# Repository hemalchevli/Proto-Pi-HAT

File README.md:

Prototying board for the raspberry pi B+. CC-BY-SA-4.0

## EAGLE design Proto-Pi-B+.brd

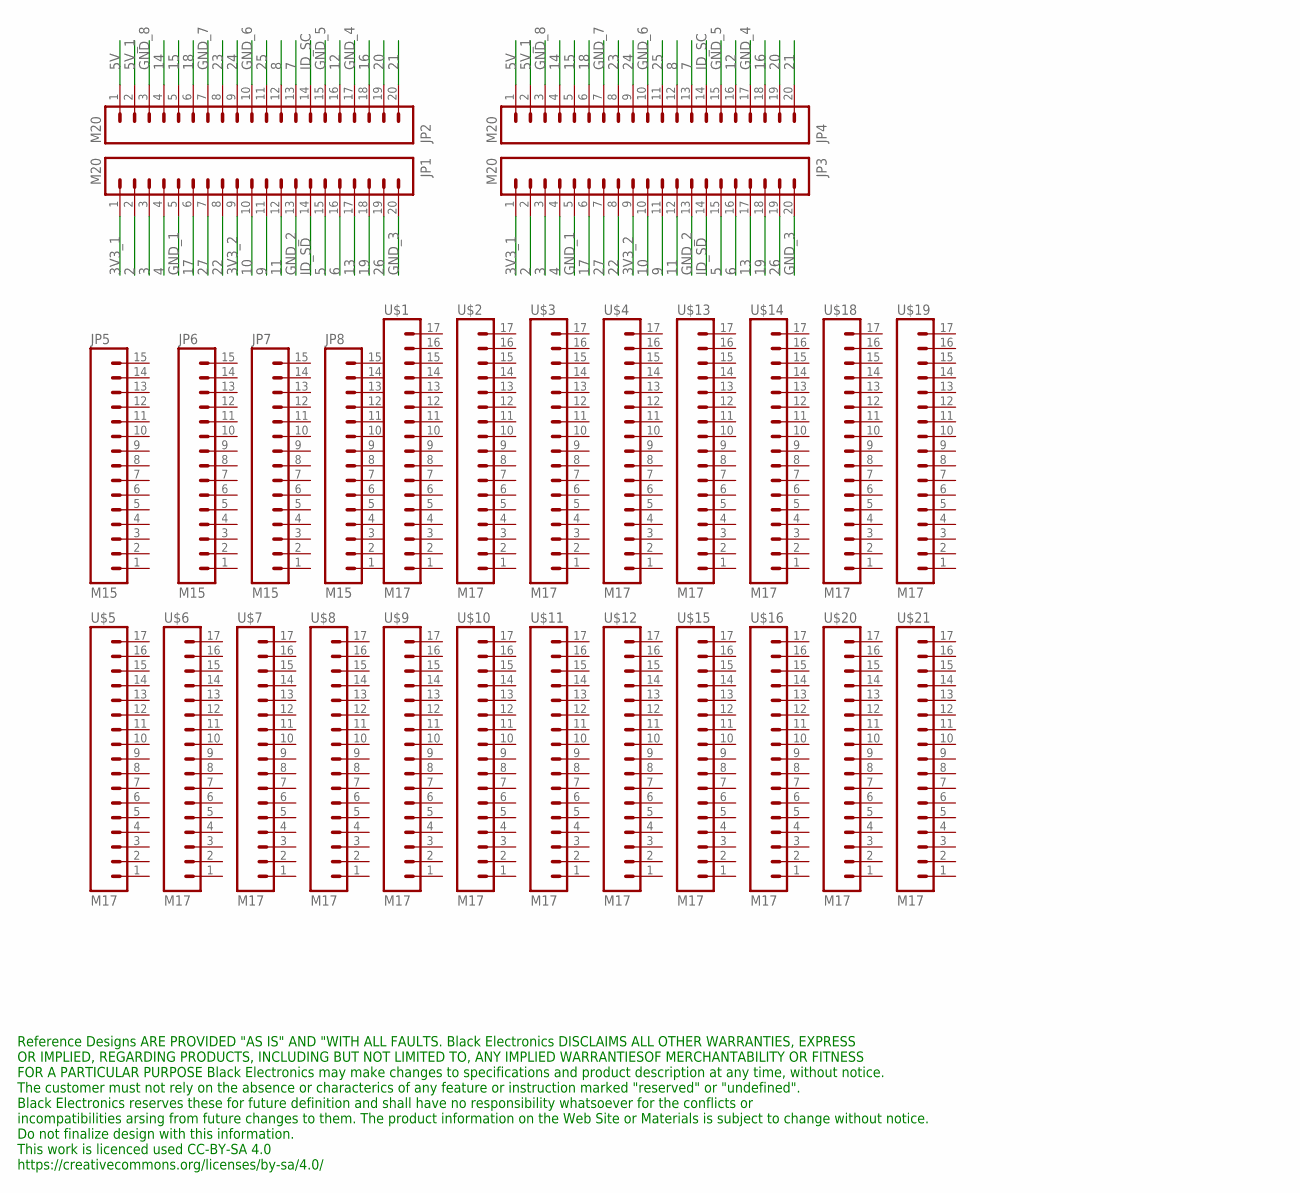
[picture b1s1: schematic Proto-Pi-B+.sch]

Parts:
JP1, JP2, JP3, JP4: M20; 1X20
JP5, JP6, JP7, JP8: M15; 1X15
U$1, U$2, U$3, U$4, U$5, U$6, U$7, U$8, U$9, U$10, U$11, U$12, U$13, U$14, U$15, U$16, U$18, U$19, U$20, U$21: M17; 1X17

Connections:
2: JP1.2, JP3.2
3: JP1.3, JP3.3
3V3_1: JP1.1, JP3.1
3V3_2: JP1.9, JP3.9
4: JP1.4, JP3.4
5: JP1.15, JP3.15
5V: JP2.1, JP4.1
5V_1: JP2.2, JP4.2
6: JP1.16, JP3.16
7: JP2.13, JP4.13
8: JP2.12, JP4.12
9: JP1.11, JP3.11
10: JP1.10, JP3.10
11: JP1.12, JP3.12
12: JP2.16, JP4.16
13: JP1.17, JP3.17
14: JP2.4, JP4.4
15: JP2.5, JP4.5
16: JP2.18, JP4.18
17: JP1.6, JP3.6
18: JP2.6, JP4.6
19: JP1.18, JP3.18
20: JP2.19, JP4.19
21: JP2.20, JP4.20
22: JP1.8, JP3.8
23: JP2.8, JP4.8
24: JP2.9, JP4.9
25: JP2.11, JP4.11
26: JP1.19, JP3.19
27: JP1.7, JP3.7
GND_1: JP1.5, JP3.5
GND_2: JP1.13, JP3.13
GND_3: JP1.20, JP3.20
GND_4: JP2.17, JP4.17
GND_5: JP2.15, JP4.15
GND_6: JP2.10, JP4.10
GND_7: JP2.7, JP4.7
GND_8: JP2.3, JP4.3
ID_SC: JP2.14, JP4.14
ID_SD: JP1.14, JP3.14

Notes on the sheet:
Reference Designs ARE PROVIDED "AS IS" AND "WITH ALL FAULTS. Black Electronics DISCLAIMS ALL OTHER WARRANTIES, EXPRESS OR IMPLIED, REGARDING PRODUCTS, INCLUDING BUT NOT LIMITED TO, ANY IMPLIED WARRANTIESOF MERCHANTABILITY OR FITNESS FOR A PARTICULAR PURPOSE Black Electronics may make changes to spe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

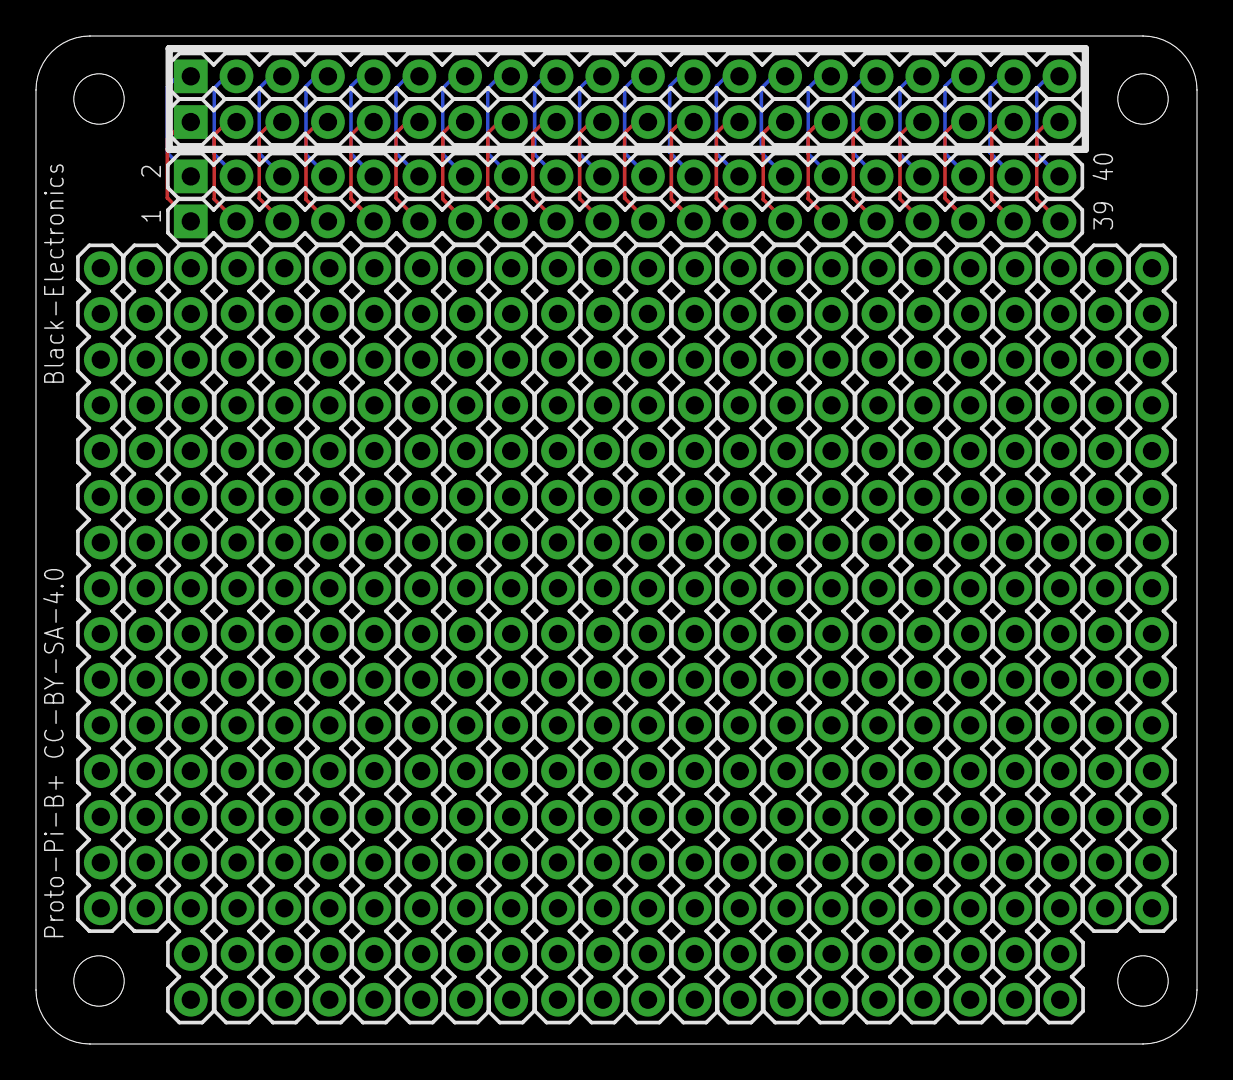
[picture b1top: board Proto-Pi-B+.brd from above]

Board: 2 copper layers, 64.5 x 56.0 mm, 28 parts (0 on the bottom side), 40 nets.

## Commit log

2015-03-15 Fab ready

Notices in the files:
Proto-Pi-B+.brd:
Proto-Pi-B+ CC-BY-SA-4.0
Proto-Pi-B+.sch:
This work is licenced used CC-BY-SA 4.0
https://creativecommons.org/licenses/by-sa/4.0
parts and their libraries:
SparkFun: Licensing: CC v3.0 Share-Alike You are welcome to use this library for commercial purposes.
